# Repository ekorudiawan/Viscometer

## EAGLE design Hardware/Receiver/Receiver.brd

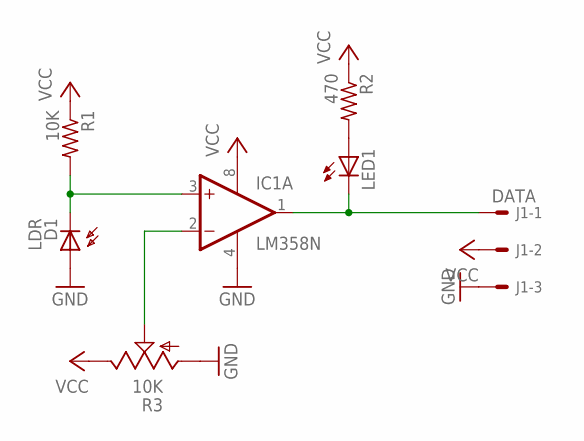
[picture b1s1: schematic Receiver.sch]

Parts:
D1: LDR; LED3MM
IC1: LM358N; DIL08
J1: DATA; 7395-03
LED1: LED3MM
R1: 10K; 0204/7
R2: 470; 0204/7
R3: 10K; CA6V

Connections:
GND: D1.A, IC1.4 (V-), J1.3, R3.A
unnamed: D1.K (C), IC1.3 (+IN), R1.2
unnamed: LED1.A, R2.2
unnamed: IC1.1 (OUT), J1.1, LED1.K (C)
unnamed: IC1.2 (-IN), R3.S
VCC: IC1.8 (V+), J1.2, R1.1, R2.1, R3.E

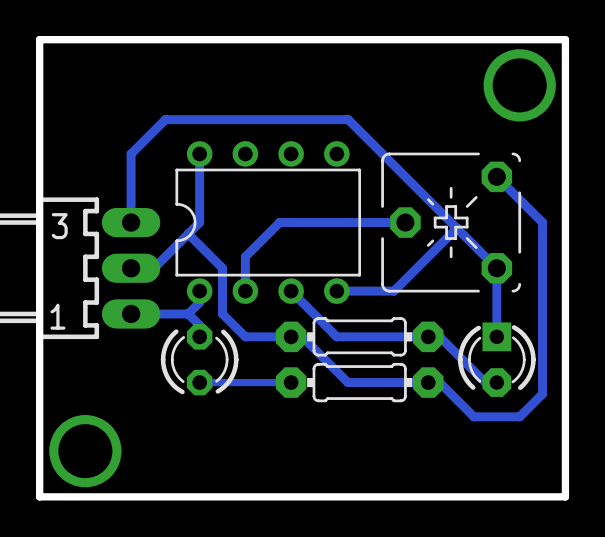
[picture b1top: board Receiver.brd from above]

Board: 2 copper layers, 29.2 x 25.4 mm, 7 parts (0 on the bottom side), 6 nets.

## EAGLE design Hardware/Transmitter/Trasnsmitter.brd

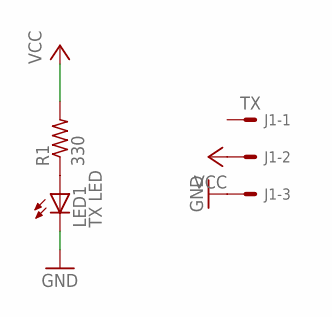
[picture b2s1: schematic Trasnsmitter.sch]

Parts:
J1: TX; 7395-03
LED1: TX LED; LED5MM
R1: 330; 0204/7

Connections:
GND: J1.3, LED1.K (C)
unnamed: LED1.A, R1.1
VCC: J1.2, R1.2

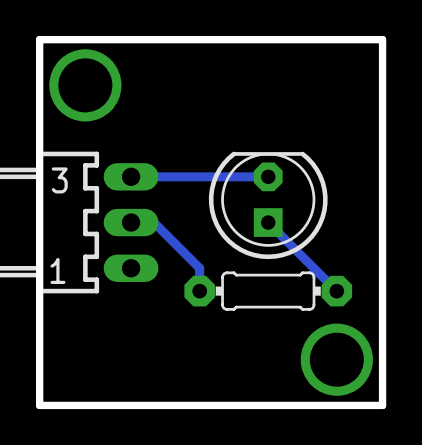
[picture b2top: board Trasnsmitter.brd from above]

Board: 2 copper layers, 19.1 x 20.3 mm, 3 parts (0 on the bottom side), 3 nets.

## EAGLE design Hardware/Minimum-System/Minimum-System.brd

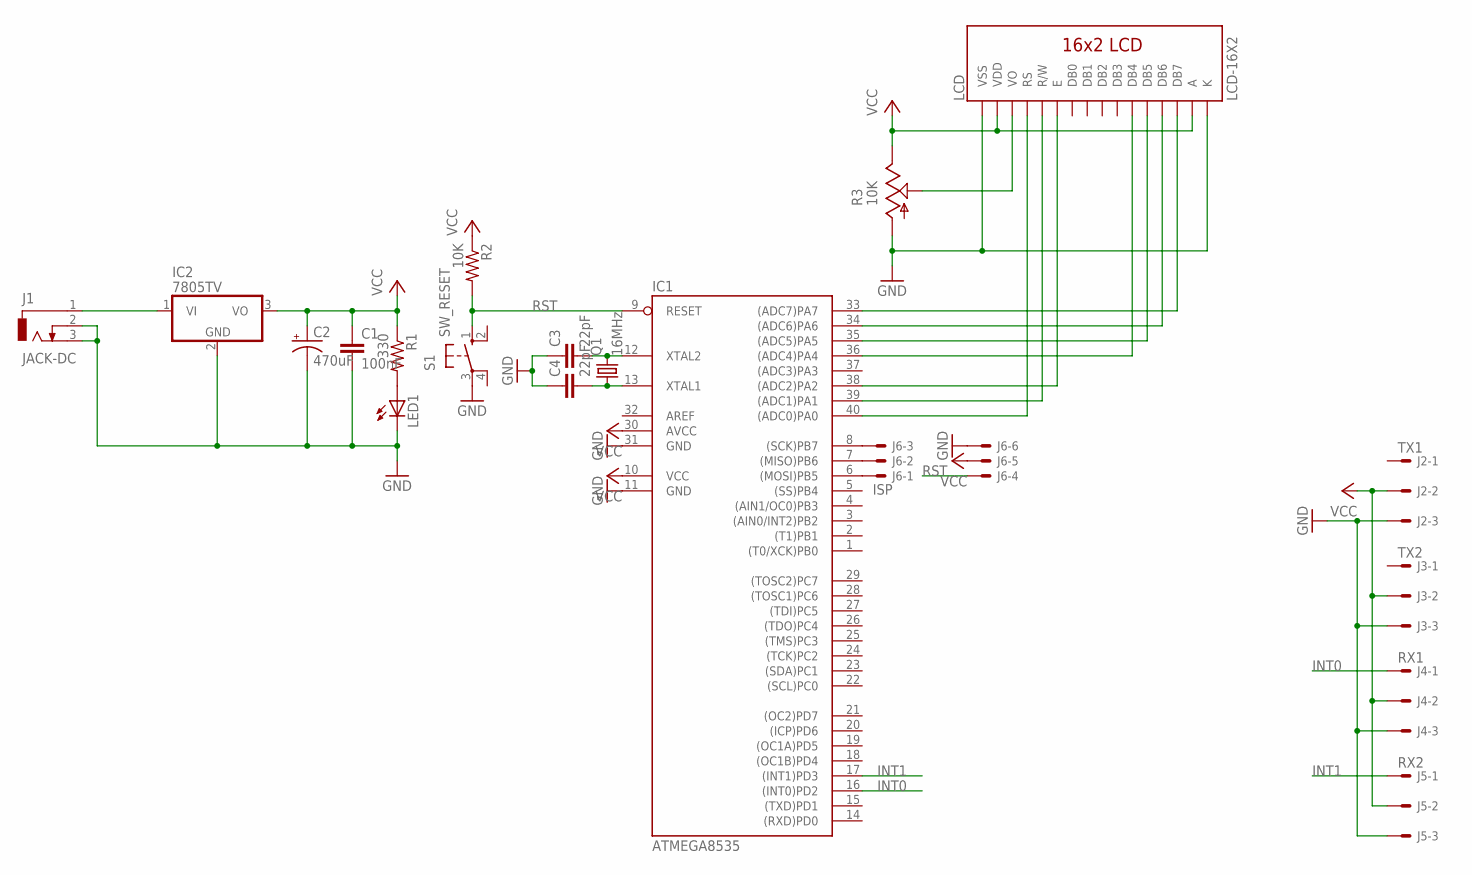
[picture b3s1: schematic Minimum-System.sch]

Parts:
C1: 100nF; C025-024X044
C2: 470uF; E2,5-6
C3, C4: 22pF; C025-024X044
IC1: ATMEGA8535; DIL40
IC2: 7805TV; TO220V
J1: JACK-DC; DCJ0202
J2: TX1; 7395-03
J3: TX2; 7395-03
J4: RX1; 7395-03
J5: RX2; 7395-03
J6: ISP; 6410-06
LCD: LCD-16X2
LED1: LED3MM
Q1: 16MHz; HC49/S
R1: 330; 0204/7
R2: 10K; 0204/7
R3: 10K; CA6V
S1: SW_RESET; B3F-10XX

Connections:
GND: C1.2, C2.-, C3.1, C4.1, IC1.11 (GND), IC1.31 (GND), IC2.2 (GND), J1.2, J1.3, J2.3, J3.3, J4.3, J5.3, J6.6, LCD.1 (VSS), LCD.16 (K), LED1.K (C), R3.A, S1.3
INT0: IC1.16 ((INT0)PD2), J4.1
INT1: IC1.17 ((INT1)PD3), J5.1
unnamed: LED1.A, R1.2
unnamed: IC1.34 ((ADC6)PA6), LCD.13 (DB6)
unnamed: IC1.33 ((ADC7)PA7), LCD.14 (DB7)
unnamed: IC2.1 (VI), J1.1
unnamed: C3.2, IC1.12 (XTAL2), Q1.2
unnamed: C4.2, IC1.13 (XTAL1), Q1.1
unnamed: LCD.3 (VO), R3.S
unnamed: IC1.40 ((ADC0)PA0), LCD.4 (RS)
unnamed: IC1.39 ((ADC1)PA1), LCD.5 (R/W)
unnamed: IC1.38 ((ADC2)PA2), LCD.6 (E)
unnamed: IC1.36 ((ADC4)PA4), LCD.11 (DB4)
unnamed: IC1.35 ((ADC5)PA5), LCD.12 (DB5)
unnamed: IC1.6 ((MOSI)PB5), J6.1
unnamed: IC1.7 ((MISO)PB6), J6.2
unnamed: IC1.8 ((SCK)PB7), J6.3
RST: IC1.9 (RESET), J6.4, R2.2, S1.1 (S)
VCC: C1.1, C2.+, IC1.10 (VCC), IC1.30 (AVCC), IC2.3 (VO), J2.2, J3.2, J4.2, J5.2, J6.5, LCD.2 (VDD), LCD.15 (A), R1.1, R2.1, R3.E

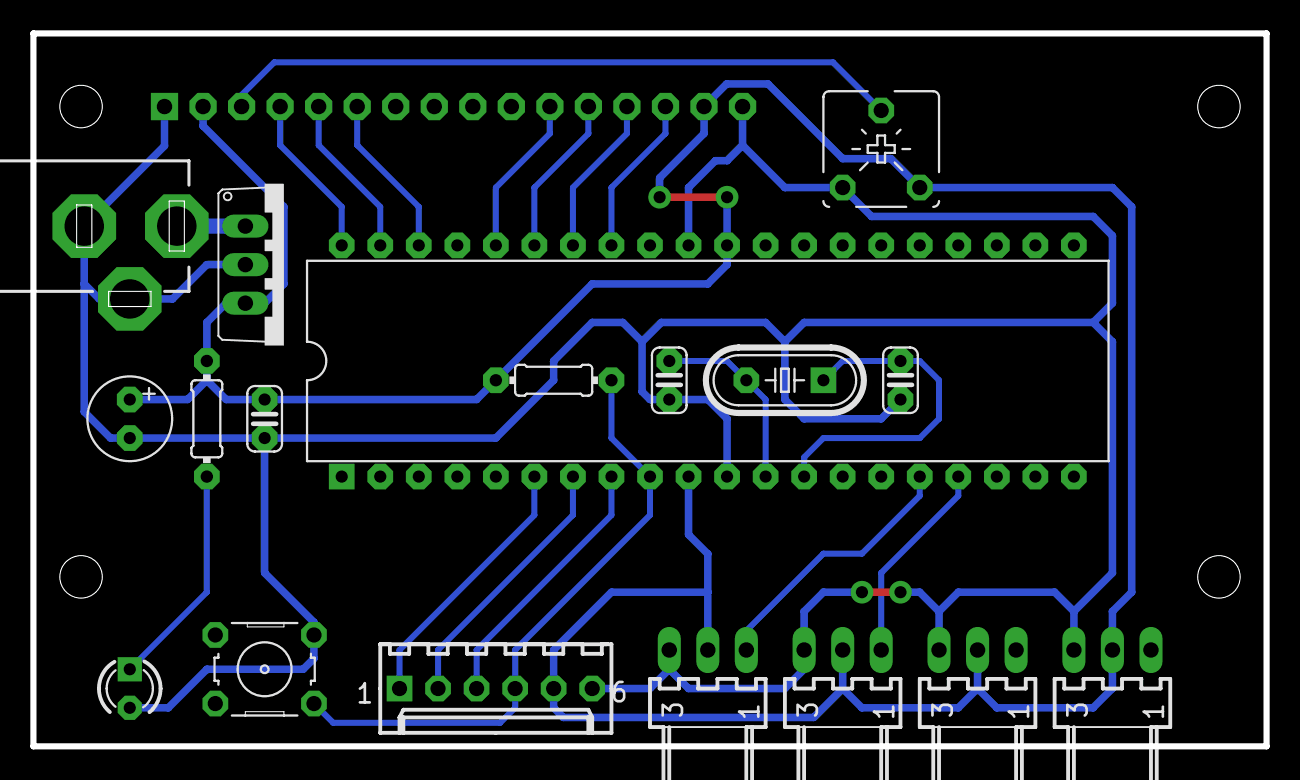
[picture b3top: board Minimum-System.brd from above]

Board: 2 copper layers, 81.3 x 47.0 mm, 19 parts (0 on the bottom side), 20 nets.

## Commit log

2017-10-03 Added HW & SW Source Files
